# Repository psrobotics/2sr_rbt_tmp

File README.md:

# 2sr_rbt_tmp
2sr_rbt_tmp

## Battery

## Revise 0729

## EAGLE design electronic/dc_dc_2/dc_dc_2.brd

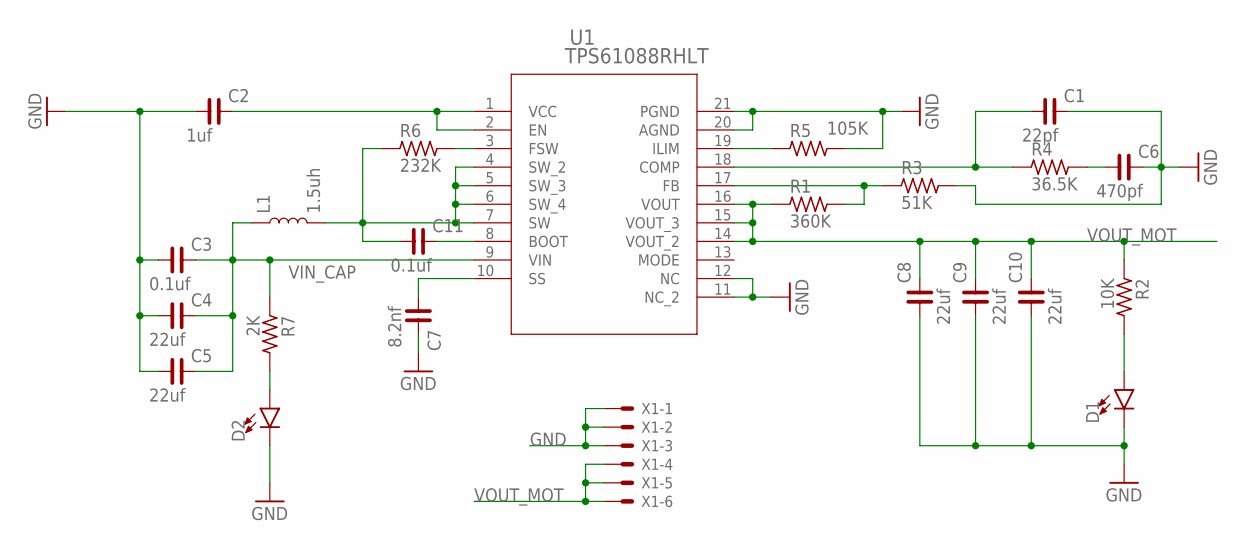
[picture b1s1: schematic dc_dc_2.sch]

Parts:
C1: 22pf; C0603
C2: 1uf; C0603
C3: 0.1uf; C1210
C4, C5, C8, C9, C10: 22uf; C1210
C6: 470pf; C0603
C7: 8.2nf; C0603
C11: 0.1uf; C0603
D1, D2: LED0603; LED-0603
L1: 1.5uh; CR75
R1: 360K; R0603
R2: 10K; R0603
R3: 51K; R0603
R4: 36.5K; R0603
R5: 105K; R0603
R6: 232K; R0603
R7: 2K; R0603
U1: TPS61088RHLT; RHL0020A_TEX
X1: 22-23-2061

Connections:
GND: C1.2, C2.1, C3.1, C4.1, C5.1, C6.2, C7.2, C8.1, C9.1, C10.1, D1.C, D2.C, R3.2, R5.2, U1.11 (NC_2), U1.12 (NC), U1.20 (AGND), U1.21 (PGND), X1.1, X1.2, X1.3
unnamed: C7.1, U1.10 (SS)
unnamed: R5.1, U1.19 (ILIM)
unnamed: C1.1, R4.1, U1.18 (COMP)
unnamed: C6.1, R4.2
unnamed: C2.2, U1.1 (VCC), U1.2 (EN)
unnamed: D2.A, R7.2
unnamed: R1.2, R3.1, U1.17 (FB)
unnamed: D1.A, R2.2
unnamed: C11.2, U1.8 (BOOT)
unnamed: C11.1, L1.P$2 (2), R6.1, U1.4 (SW_2), U1.5 (SW_3), U1.6 (SW_4), U1.7 (SW)
unnamed: R6.2, U1.3 (FSW)
VIN_CAP: C3.2, C4.2, C5.2, L1.P$1 (1), R7.1, U1.9 (VIN)
VOUT_MOT: C8.2, C9.2, C10.2, R1.1, R2.1, U1.14 (VOUT_2), U1.15 (VOUT_3), U1.16 (VOUT), X1.4, X1.5, X1.6

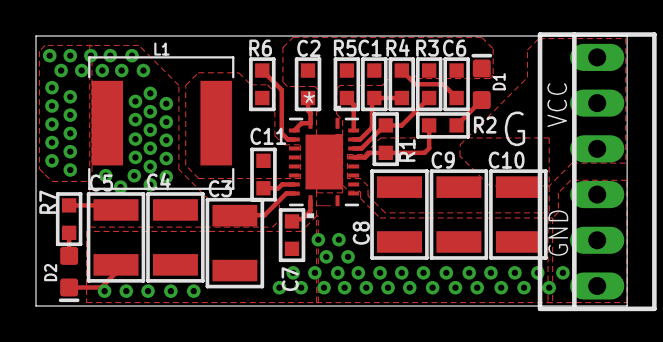
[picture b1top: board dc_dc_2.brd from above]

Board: 2 copper layers, 32.8 x 15.0 mm, 23 parts (0 on the bottom side), 14 nets.

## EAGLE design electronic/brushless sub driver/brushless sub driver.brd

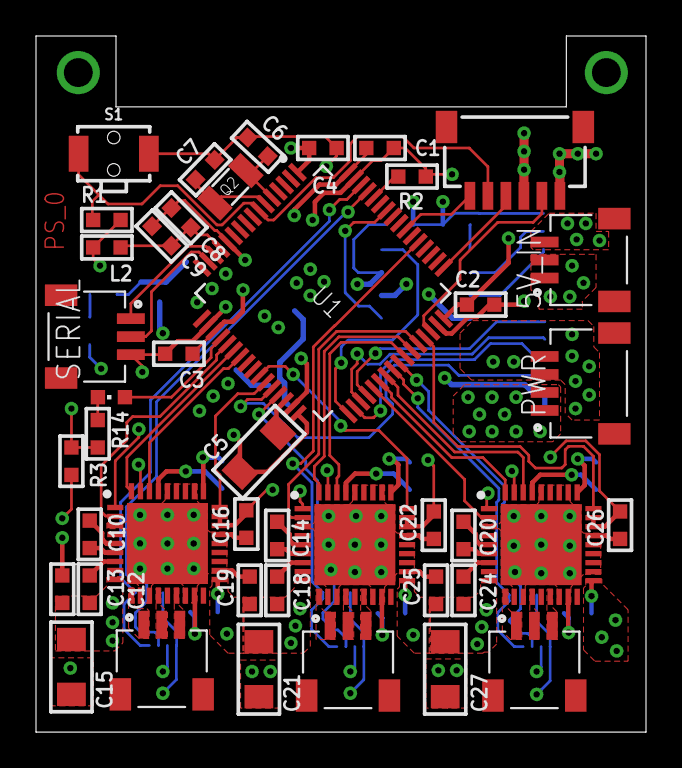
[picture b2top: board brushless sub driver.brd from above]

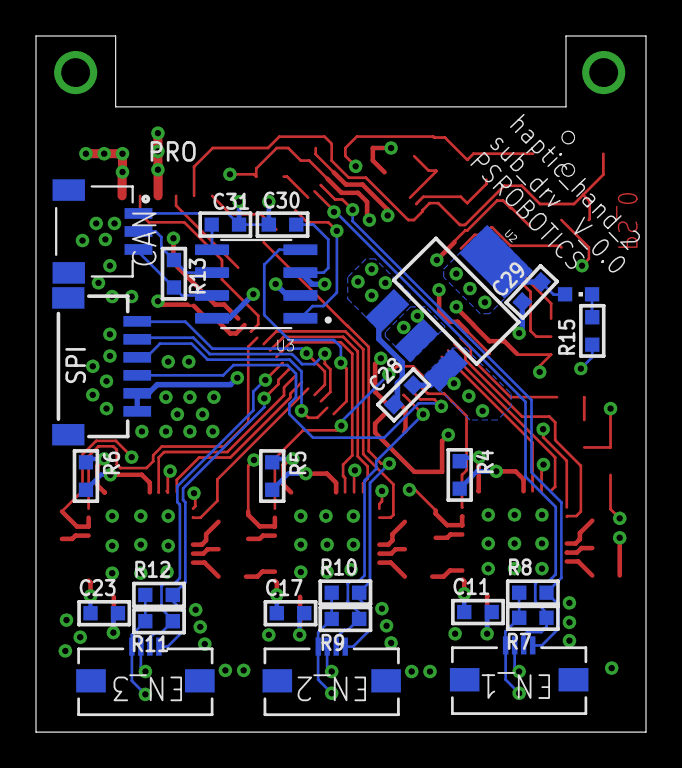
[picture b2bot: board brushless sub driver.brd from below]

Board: 4 copper layers, 33.9 x 38.7 mm, 69 parts (26 on the bottom side), 70 nets.

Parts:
5V_IN: SM03B-SRSS-TB(LF)(SN); JST_SM03B-SRSS-TB(LF)(SN)
C1, C2, C3, C11, C12, C13, C17, C18, C19, C23, C24, C25: 0.1uf; C0603
C4, C8, C30, C31: 1uf; C0603
C5: 4.7uf; C1206
C6, C7: 22pf; C0603
C9, C10, C16, C22: 10nf; C0603
C14, C20, C26: 470nf; C0603
C15, C21, C27: 100uf; C1206
C28: 100nf; C0603
C29: 10uf; C0603
CAN: SM03B-SRSS-TB(LF)(SN); JST_SM03B-SRSS-TB(LF)(SN)
EN_1, EN_2, EN_3: 54550-0494; CON4_1X4_DRB2_MOL
IC1, IC2, IC3: DRV8313RHHR; QFN50P600X600X100-37N
L2: 22uh; PM0603
LED1, LED2: CHIPLED_0603
MOT1, MOT2, MOT3: SM03B-SRSS-TB(LF)(SN); JST_SM03B-SRSS-TB(LF)(SN)
PRO: SM06B-SRSS-TB; SM06B
PWR: SM04B-SRSS-TB(LF)(SN); JST_SM04B-SRSS-TB(LF)(SN)
Q2: 32.768khz; 3.2X1.5
R1, R2: 4.7k; R0603
R3: 0; R0603
R4, R5, R6: 10K; R0603
R7, R8, R9, R10, R11, R12: 2.4k; R0603
R13: 120; R0603
R14: 2K; R0603
R15: 3K; R0603
S1: MOMENTARY-SWITCH-SPST-SMD-RIGHT-ANGLE; TACTILE_SWITCH_SMD_RIGHT_ANGLE
SERIAL: SM03B-SRSS-TB(LF)(SN); JST_SM03B-SRSS-TB(LF)(SN)
SPI: SM06B-SRSS-TB; SM06B
U1: STMICROELECTRONICS_STM32F446RET6STMICROELECTRONIC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; STMICROELECTRONICS_STM32F446RET6_0
U2: SOT223
U3: MCP2561-E/SN; SOIC127P600X175-8N

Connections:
3V3: C1.1, C2.1, C3.1, C4.1, C5.1, C29.2, EN_1.1, EN_2.1, EN_3.1, L2.2, LED2.A, PRO.1, R1.2, R7.1, R8.1, R9.1, R10.1, R11.1, R12.1, U1.1, U1.19, U1.32, U1.48, U1.64, U2.2, U2.4
5V: 5V_IN.1, 5V_IN.2, C28.2, C30.2, U2.3, U3.3
AGND: C11.2, C12.1, C14.2, C15.1, C17.2, C18.1, C20.2, C21.1, C23.2, C24.1, C26.2, C27.1, IC1.3, IC1.11, IC1.12, IC1.16, IC1.17, IC1.20, IC1.21, IC1.22, IC1.23, IC1.24, IC1.29, IC1.30, IC1.31, IC1.32, IC1.37, IC2.3, IC2.11, IC2.12, IC2.16, IC2.17, IC2.20, IC2.21, IC2.22, IC2.23, IC2.24, IC2.29, IC2.30, IC2.31, IC2.32, IC2.37, IC3.3, IC3.11, IC3.12, IC3.16, IC3.17, IC3.20, IC3.21, IC3.22, IC3.23, IC3.24, IC3.29, IC3.30, IC3.31, IC3.32, IC3.37, PWR.3, PWR.4, R3.1
CAN_H: CAN.3, R13.2, U3.7
CAN_L: CAN.2, R13.1, U3.6
CAN_RX: U1.33, U3.4
CAN_TX: U1.58, U3.1
DEBUG_LED: LED1.A, U1.20
DEBUG_RX: SERIAL.2, U1.15
DEBUG_TX: SERIAL.1, U1.14
FAU_1: IC1.28, R4.1
FAU_2: IC2.28, R5.1
FAU_3: IC3.28, R6.1
GND: 5V_IN.3, C1.2, C2.2, C3.2, C4.2, C6.2, C7.2, C8.1, C9.1, C28.1, C29.1, C30.1, C31.2, CAN.1, EN_1.2, EN_2.2, EN_3.2, PRO.3, R2.1, R3.2, R14.1, R15.1, S1.2, SERIAL.3, SPI.5, SPI.6, U1.12, U1.18, U1.31, U1.47, U1.63, U2.1, U3.2, U3.8
IN_U_1: IC1.2, U1.21
IN_U_2: IC2.2, U1.44
IN_U_3: IC3.2, U1.37
IN_V_1: IC1.36, U1.22
IN_V_2: IC2.36, U1.43
IN_V_3: IC3.36, U1.38
IN_W_1: IC1.34, U1.23
IN_W_2: IC2.34, U1.42
IN_W_3: IC3.34, U1.39
MOT_3V3_1: C14.1, IC1.1, IC1.25, IC1.26, IC1.33, IC1.35, R4.2
MOT_3V3_2: C20.1, IC2.1, IC2.25, IC2.26, IC2.33, IC2.35, R5.2
MOT_3V3_3: C26.1, IC3.1, IC3.25, IC3.26, IC3.33, IC3.35, R6.2
unnamed: C5.2, U1.30
unnamed: R2.2, U1.60
unnamed: C7.1, Q2.1, U1.6
unnamed: C10.2, IC1.5
unnamed: C6.1, Q2.2, U1.5
unnamed: C10.1, IC1.6
unnamed: C13.2, IC1.7
unnamed: C16.2, IC2.5
unnamed: C16.1, IC2.6
unnamed: C19.2, IC2.7
unnamed: C22.2, IC3.5
unnamed: C22.1, IC3.6
unnamed: C25.2, IC3.7
unnamed: C31.1, U3.5
unnamed: LED2.C, R15.2
unnamed: LED1.C, R14.2
RST: PRO.5, R1.1, S1.1, U1.7
SCL_1: EN_1.3, R7.2, U1.61
SCL_2: EN_2.3, R9.2, U1.29
SCL_3: EN_3.3, R11.2, U1.41
SDA_1: EN_1.4, R8.2, U1.62
SDA_2: EN_2.4, R10.2, U1.53
SDA_3: EN_3.4, R12.2, U1.40
SLP_1: IC1.27, U1.27
SLP_2: IC2.27, U1.26
SLP_3: IC3.27, U1.45
SPI_CLK: SPI.3, U1.34
SPI_CS: SPI.4, U1.28
SPI_MISO: SPI.2, U1.35
SPI_MOSI: SPI.1, U1.36
SWCLK: PRO.4, U1.49
SWDIO: PRO.2, U1.46
SWO: PRO.6, U1.55
U1: IC1.10, MOT1.1
U2: IC2.10, MOT2.1
U3: IC3.10, MOT3.1
V1: IC1.13, MOT1.2
V2: IC2.13, MOT2.2
V3: IC3.13, MOT3.2
VDDA: C8.2, C9.2, L2.1, U1.13
VM: C11.1, C12.2, C13.1, C15.2, C17.1, C18.2, C19.1, C21.2, C23.1, C24.2, C25.1, C27.2, IC1.9, IC1.19, IC2.9, IC2.19, IC3.9, IC3.19, PWR.1, PWR.2
W1: IC1.15, MOT1.3
W2: IC2.15, MOT2.3
W3: IC3.15, MOT3.3

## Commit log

2022-06-27 add: 0628 -1
2022-06-27 add: 0628 -2
2022-07-28 add: 0729

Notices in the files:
parts and their libraries:
rc-master-smd: Copyright (C) 2007, Bob Starr
SparkFun-Switches: Licensing: Creative Commons ShareAlike 4.0 International - https://creativecommons.org/licenses/by-sa/4.0
crystal-geyer_V1_0: Copyright: Geyer-Electronic
COPYRIGHT: Copyright (C) 2018 Accelerated Designs. All rights reserved
